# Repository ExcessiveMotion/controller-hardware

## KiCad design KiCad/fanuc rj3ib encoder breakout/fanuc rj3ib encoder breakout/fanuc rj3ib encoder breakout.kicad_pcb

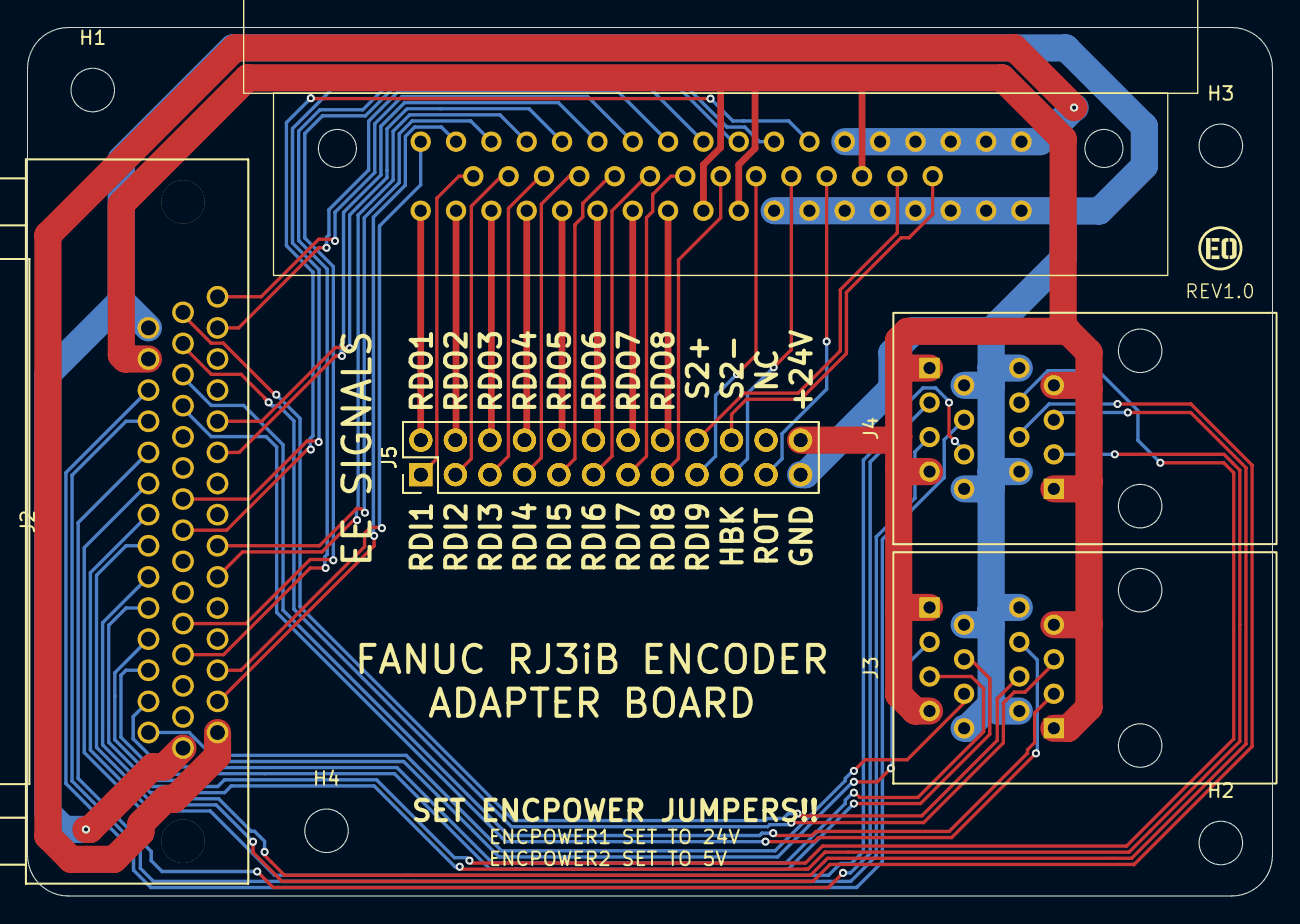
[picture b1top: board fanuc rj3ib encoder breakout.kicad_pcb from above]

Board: 2 copper layers, 91.6 x 63.9 mm, 10 parts (0 on the bottom side), 52 nets.

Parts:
H1, H2, H3, H4: MountingHole; MountingHole_3.2mm_M3_ISO7380
J1: Conn_01x50_Pin; HONDA_MR50_MALE_RIGHT_ANGLE
J2: L77HDB44SD1CH4F; CONN_L77HDB44SD1CH4F_AMP
J3, J4: E5908-0T0343-L; RJ45_E5908-0T0343-L
J5, J5#2: Conn_02x12_Odd_Even; PinHeader_2x12_P2.54mm_Vertical

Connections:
ENC1TX/RX+: J1.1, J2.3
ENC1TX/RX-: J1.2, J2.2
ENC2TX/RX+: J1.3, J2.7
ENC2TX/RX-: J1.4, J2.6
ENC3TX/RX+: J1.5, J2.11
ENC3TX/RX-: J1.6, J2.10
ENC4TX/RX+: J1.7, J2.15
ENC4TX/RX-: J1.8, J2.14
ENC5TX/RX+: J1.9, J2.20
ENC5TX/RX-: J1.10, J2.19
ENC6TX/RX+: J1.11, J2.24
ENC6TX/RX-: J1.12, J2.23
ENC7RX+: J2.30, J3.4
ENC7RX-: J2.29, J3.5
ENC7TX/RX+: J2.28, J3.3
ENC7TX/RX-: J2.27, J3.6
ENC8RX+: J2.34, J3.12
ENC8RX-: J2.33, J3.13
ENC8TX/RX+: J2.32, J3.11
ENC8TX/RX-: J2.31, J3.14
ENC9RX+: J2.38, J4.4
ENC9RX-: J2.37, J4.5
ENC9TX/RX+: J2.36, J4.3
ENC9TX/RX-: J2.35, J4.6
ENC10RX+: J2.42, J4.12
ENC10RX-: J2.41, J4.13
ENC10TX/RX+: J2.40, J4.11
ENC10TX/RX-: J2.39, J4.14
ENCPOWER1: J1.30, J1.41, J1.42, J2.43, J3.1, J3.7, J3.9, J3.15, J4.1, J4.7, J4.9, J4.15, J5.24, J5#2.24
ENCPOWER2: J1.13, J1.14, J1.15, J1.16, J1.17, J1.18, J2.1
GND: J1.43, J1.44, J1.45, J1.46, J1.47, J1.48, J1.49, J1.50, J2.16, J2.44, J3.2, J3.8, J3.10, J3.16, J4.2, J4.8, J4.10, J4.16, J5.23, J5#2.23
HBK: J1.28, J5.19, J5#2.19
RDI1: J1.19, J5.1, J5#2.1
RDI2: J1.20, J5.3, J5#2.3
RDI3: J1.21, J5.5, J5#2.5
RDI4: J1.22, J5.7, J5#2.7
RDI5: J1.23, J5.9, J5#2.9
RDI6: J1.24, J5.11, J5#2.11
RDI7: J1.25, J5.13, J5#2.13
RDI8: J1.26, J5.15, J5#2.15
RDI9(PPABN): J1.27, J5.17, J5#2.17
RDO1: J1.33, J5.2, J5#2.2
RDO2: J1.34, J5.4, J5#2.4
RDO3: J1.35, J5.6, J5#2.6
RDO4: J1.36, J5.8, J5#2.8
RDO5: J1.37, J5.10, J5#2.10
RDO6: J1.38, J5.12, J5#2.12
RDO7: J1.39, J5.14, J5#2.14
RDO8: J1.40, J5.16, J5#2.16
ROT: J1.29, J5.21, J5#2.21
S2+: J1.31, J5.18, J5#2.18
S2-: J1.32, J5.20, J5#2.20

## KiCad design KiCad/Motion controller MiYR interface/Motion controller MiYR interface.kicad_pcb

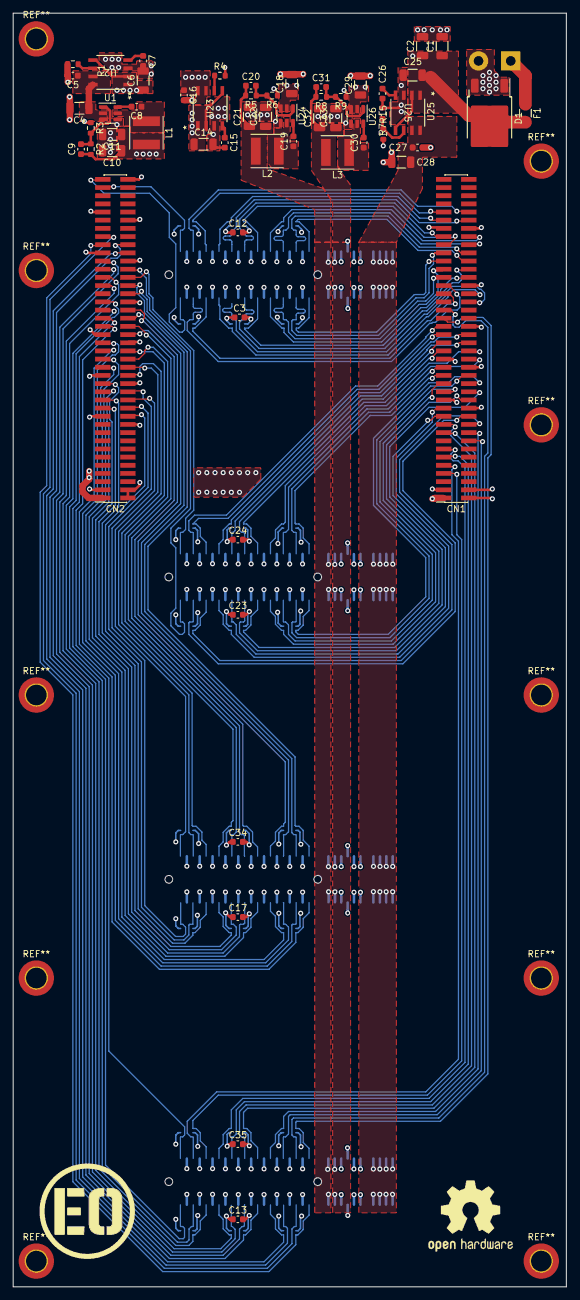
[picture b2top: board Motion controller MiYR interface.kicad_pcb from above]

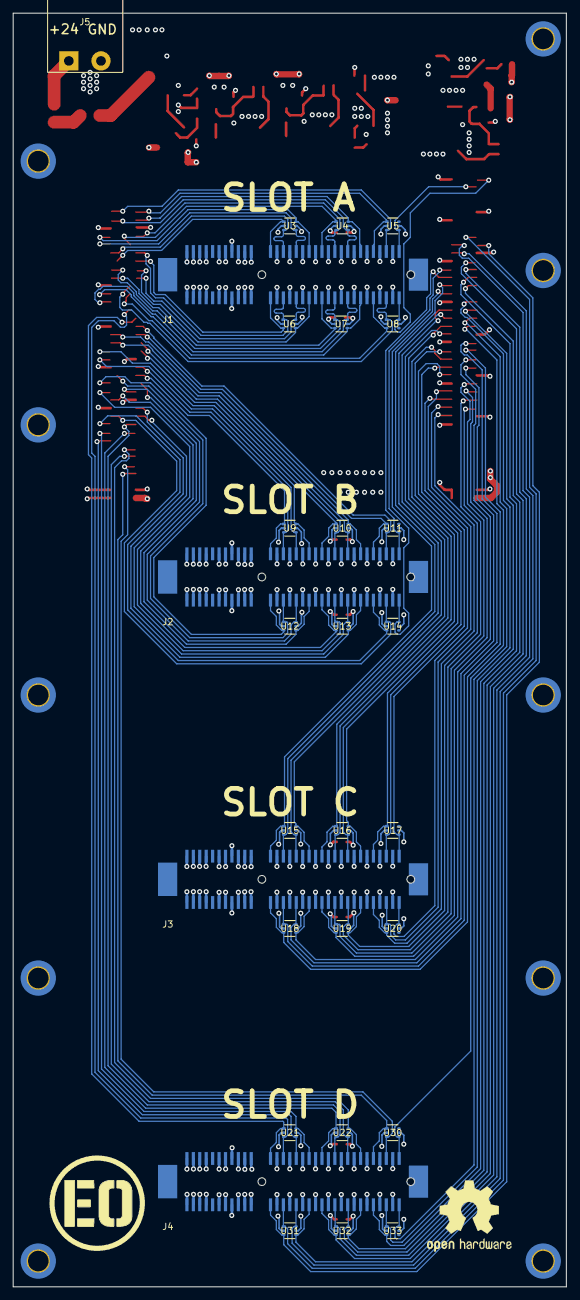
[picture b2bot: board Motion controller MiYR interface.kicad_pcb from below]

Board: 4 copper layers, 86.0 x 198.0 mm, 87 parts (29 on the bottom side), 113 nets.

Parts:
C1, C2, C4, C6, C10, C11, C14, C18, C21, C22, C25, C28, C29, C32, C33: 10uf; C_1206_3216Metric
C3, C5, C7, C8, C12, C13, C15, C16, C17, C19, C23, C24, C26, C27, C30, C34, C35: .1uf; C_0603_1608Metric
C9, C20, C31: 100pf; C_0603_1608Metric
CN1, CN2: Conn_02x40_Odd_Even; PinHeader_2x40_P1.27mm_Vertical_SMD_FLIPPED
D1: D; TO-252-3_TabPin2
F1: 10A; Fuse_1206_3216Metric
J1, J2, J3, J4: 10061913-111PLF; PCI_64_SMD_CONNECTOR
J5: Conn_01x02_Pin; 1x02_P5.00mm_Horizontal_terminal_block
L1, L2: 10uH; L_Taiyo-Yuden_MD-5050
L3: 6.8uH; L_Taiyo-Yuden_MD-5050
R1, R4, R7, R15: 100k; R_0603_1608Metric
R2: 158k; R_0603_1608Metric
R3, R6, R9: 30.1k; R_0603_1608Metric
R5: 158K; R_0603_1608Metric
R8: 93.1k; R_0603_1608Metric
U1, U24, U26: AP63201WU; TSOT-23-6
U2, U23, U25: AOZ1360AIL; AOZ1360AIL_AOS
U3, U4, U5, U6, U7, U8, U9, U10, U11, U12, U13, U14, U15, U16, U17, U18, U19, U20, U21, U22, U30, U31, U32, U33: D1213A-04S-7; SOT-363_DIO

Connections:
+3.3V: C3.1, C12.1, C13.1, C17.1, C23.1, C24.1, C34.1, C35.1, CN1.3, CN2.3, U3.5 (VCC), U4.5 (VCC), U5.5 (VCC), U6.5 (VCC), U7.5 (VCC), U8.5 (VCC), U9.5 (VCC), U10.5 (VCC), U11.5 (VCC), U12.5 (VCC), U13.5 (VCC), U14.5 (VCC), U15.5 (VCC), U16.5 (VCC), U17.5 (VCC), U18.5 (VCC), U19.5 (VCC), U20.5 (VCC), U21.5 (VCC), U22.5 (VCC), U30.5 (VCC), U31.5 (VCC), U32.5 (VCC), U33.5 (VCC)
+3.3VP: C31.1, C32.1, C33.1, J1.P$A10 (A10), J1.P$B10 (B10), J2.P$A10 (A10), J2.P$B10 (B10), J3.P$A10 (A10), J3.P$B10 (B10), J4.P$A10 (A10), J4.P$B10 (B10), L3.2, R8.2
+5V: C9.1, C10.1, C11.1, CN1.1, CN2.1, L1.2, R2.2
+5VP: C20.1, C21.1, C22.1, J1.P$A11 (A11), J1.P$B11 (B11), J2.P$A11 (A11), J2.P$B11 (B11), J3.P$A11 (A11), J3.P$B11 (B11), J4.P$A11 (A11), J4.P$B11 (B11), L2.2, R5.2
+24V: C1.1, C2.1, C6.1, C14.1, C25.1, D1.1 (K), F1.2, U2.1 (IN), U2.2 (IN), U2.5 (EN), U23.1 (IN), U23.2 (IN), U23.5 (EN), U25.1 (IN), U25.2 (IN), U25.5 (EN)
GND: C1.2, C2.2, C3.2, C4.2, C5.2, C6.2, C7.2, C10.2, C11.2, C12.2, C13.2, C14.2, C15.2, C16.2, C17.2, C18.2, C21.2, C22.2, C23.2, C24.2, C25.2, C26.2, C27.2, C28.2, C29.2, C32.2, C33.2, C34.2, C35.2, CN1.2, CN1.4, CN1.24, CN1.25, CN1.34, CN1.35, CN1.44, CN1.54, CN1.67, CN1.68, CN2.2, CN2.4, CN2.20, CN2.21, CN2.30, CN2.31, CN2.40, CN2.41, CN2.50, CN2.60, CN2.61, CN2.70, CN2.71, CN2.80, D1.2 (A), J1.P$A6 (A6), J1.P$A7 (A7), J1.P$A8 (A8), J1.P$A9 (A9), J1.P$A13 (A13), J1.P$A15 (A15), J1.P$A17 (A17), J1.P$A19 (A19), J1.P$A21 (A21), J1.P$A23 (A23), J1.P$A25 (A25), J1.P$A27 (A27), J1.P$A29 (A29), J1.P$A31 (A31), J1.P$B6 (B6), J1.P$B7 (B7), J1.P$B8 (B8), J1.P$B9 (B9), J1.P$B13 (B13), J1.P$B15 (B15), J1.P$B17 (B17), J1.P$B19 (B19), J1.P$B21 (B21), J1.P$B23 (B23), J1.P$B25 (B25), J1.P$B27 (B27), J1.P$B29 (B29), J1.P$B31 (B31), J2.P$A6 (A6), J2.P$A7 (A7), J2.P$A8 (A8), J2.P$A9 (A9), J2.P$A13 (A13), J2.P$A15 (A15), J2.P$A17 (A17), J2.P$A19 (A19), J2.P$A21 (A21), J2.P$A23 (A23), J2.P$A25 (A25), J2.P$A27 (A27), J2.P$A29 (A29), J2.P$A31 (A31), J2.P$B6 (B6), J2.P$B7 (B7), J2.P$B8 (B8), J2.P$B9 (B9), J2.P$B13 (B13), J2.P$B15 (B15), J2.P$B17 (B17), J2.P$B19 (B19), J2.P$B21 (B21), J2.P$B23 (B23), J2.P$B25 (B25), J2.P$B27 (B27), J2.P$B29 (B29), J2.P$B31 (B31), J3.P$A6 (A6), J3.P$A7 (A7), J3.P$A8 (A8), J3.P$A9 (A9), J3.P$A13 (A13), J3.P$A15 (A15), J3.P$A17 (A17), J3.P$A19 (A19), J3.P$A21 (A21), J3.P$A23 (A23), J3.P$A25 (A25), J3.P$A27 (A27), J3.P$A29 (A29), J3.P$A31 (A31), J3.P$B6 (B6), J3.P$B7 (B7), J3.P$B8 (B8), J3.P$B9 (B9), J3.P$B13 (B13), J3.P$B15 (B15), J3.P$B17 (B17), J3.P$B19 (B19), J3.P$B21 (B21), J3.P$B23 (B23), J3.P$B25 (B25), J3.P$B27 (B27), J3.P$B29 (B29), J3.P$B31 (B31), J4.P$A6 (A6), J4.P$A7 (A7), J4.P$A8 (A8), J4.P$A9 (A9), J4.P$A13 (A13), J4.P$A15 (A15), J4.P$A17 (A17), J4.P$A19 (A19), J4.P$A21 (A21), J4.P$A23 (A23), J4.P$A25 (A25), J4.P$A27 (A27), J4.P$A29 (A29), J4.P$A31 (A31), J4.P$B6 (B6), J4.P$B7 (B7), J4.P$B8 (B8), J4.P$B9 (B9), J4.P$B13 (B13), J4.P$B15 (B15), J4.P$B17 (B17), J4.P$B19 (B19), J4.P$B21 (B21), J4.P$B23 (B23), J4.P$B25 (B25), J4.P$B27 (B27), J4.P$B29 (B29), J4.P$B31 (B31), J5.2, R1.2, R3.1, R4.2, R6.1, R7.2, R9.1, R15.2, U1.4 (GND), U2.3 (GND), U3.2 (GND), U4.2 (GND), U5.2 (GND), U6.2 (GND), U7.2 (GND), U8.2 (GND), U9.2 (GND), U10.2 (GND), U11.2 (GND), U12.2 (GND), U13.2 (GND), U14.2 (GND), U15.2 (GND), U16.2 (GND), U17.2 (GND), U18.2 (GND), U19.2 (GND), U20.2 (GND), U21.2 (GND), U22.2 (GND), U23.3 (GND), U24.4 (GND), U25.3 (GND), U26.4 (GND), U30.2 (GND), U31.2 (GND), U32.2 (GND), U33.2 (GND)
unnamed: F1.1, J5.1
unnamed: C8.2, U1.6 (BST)
unnamed: C4.1, C5.1, U1.2 (EN), U1.3 (IN), U2.7 (OUT), U2.8 (OUT)
unnamed: C9.2, R2.1, R3.2, U1.1 (FB)
unnamed: C8.1, L1.1, U1.5 (SW)
unnamed: R1.1, U2.6 (SET)
unnamed: C7.1, U2.4 (SS)
unnamed: R4.1, U23.6 (SET)
unnamed: C15.1, U23.4 (SS)
unnamed: C19.2, U24.6 (BST)
unnamed: C16.1, C18.1, C29.1, U23.7 (OUT), U23.8 (OUT), U24.2 (EN), U24.3 (IN), U26.2 (EN), U26.3 (IN)
unnamed: C20.2, R5.1, R6.2, U24.1 (FB)
unnamed: C19.1, L2.1, U24.5 (SW)
unnamed: R7.1, R15.1, U25.6 (SET)
unnamed: C26.1, U25.4 (SS)
unnamed: C30.2, U26.6 (BST)
unnamed: C31.2, R8.1, R9.2, U26.1 (FB)
unnamed: C30.1, L3.1, U26.5 (SW)
SLOT A 24V: C27.1, C28.1, J1.P$A1 (A1), J1.P$A2 (A2), J1.P$A3 (A3), J1.P$A4 (A4), J1.P$B1 (B1), J1.P$B2 (B2), J1.P$B3 (B3), J1.P$B4 (B4), J2.P$A1 (A1), J2.P$A2 (A2), J2.P$A3 (A3), J2.P$A4 (A4), J2.P$B1 (B1), J2.P$B2 (B2), J2.P$B3 (B3), J2.P$B4 (B4), J3.P$A1 (A1), J3.P$A2 (A2), J3.P$A3 (A3), J3.P$A4 (A4), J3.P$B1 (B1), J3.P$B2 (B2), J3.P$B3 (B3), J3.P$B4 (B4), J4.P$A1 (A1), J4.P$A2 (A2), J4.P$A3 (A3), J4.P$A4 (A4), J4.P$B1 (B1), J4.P$B2 (B2), J4.P$B3 (B3), J4.P$B4 (B4), U25.7 (OUT), U25.8 (OUT)
SLOTA1N: CN1.62, J1.P$A14 (A14), U3.3 (CH2)
SLOTA1P: CN1.60, J1.P$A12 (A12), U3.1 (CH1)
SLOTA2N: CN1.66, J1.P$A18 (A18), U3.6 (CH4)
SLOTA2P: CN1.64, J1.P$A16 (A16), U3.4 (CH3)
SLOTA3N: CN1.65, J1.P$A22 (A22), U4.3 (CH2)
SLOTA3P: CN1.63, J1.P$A20 (A20), U4.1 (CH1)
SLOTA4N: CN1.69, J1.P$A26 (A26), U4.6 (CH4)
SLOTA4P: CN1.70, J1.P$A24 (A24), U4.4 (CH3)
SLOTA5N: CN1.72, J1.P$A30 (A30), U5.3 (CH2)
SLOTA5P: CN1.71, J1.P$A28 (A28), U5.1 (CH1)
SLOTA6N: CN1.61, J1.P$B14 (B14), U6.1 (CH1)
SLOTA6P: CN1.59, J1.P$B12 (B12), U6.3 (CH2)
SLOTA7N: CN1.57, J1.P$B18 (B18), U6.4 (CH3)
SLOTA7P: CN1.55, J1.P$B16 (B16), U6.6 (CH4)
SLOTA8N: CN1.58, J1.P$B22 (B22), U7.1 (CH1)
SLOTA8P: CN1.56, J1.P$B20 (B20), U7.3 (CH2)
SLOTA9N: CN1.52, J1.P$B26 (B26), U7.4 (CH3)
SLOTA9P: CN1.50, J1.P$B24 (B24), U7.6 (CH4)
SLOTA10N: CN1.53, J1.P$B30 (B30), U8.1 (CH1)
SLOTA10P: CN1.51, J1.P$B28 (B28), U8.3 (CH2)
SLOTA11N: CN2.79, J1.P$B32 (B32), U8.6 (CH4)
SLOTA11P: CN2.77, J1.P$A32 (A32), U5.4 (CH3)
SLOTB1N: CN1.33, J2.P$A14 (A14), U9.3 (CH2)
SLOTB1P: CN1.31, J2.P$A12 (A12), U9.1 (CH1)
SLOTB2N: CN1.38, J2.P$A18 (A18), U9.6 (CH4)
SLOTB2P: CN1.36, J2.P$A16 (A16), U9.4 (CH3)
SLOTB3N: CN1.39, J2.P$A22 (A22), U10.3 (CH2)
SLOTB3P: CN1.37, J2.P$A20 (A20), U10.1 (CH1)
SLOTB4N: CN1.42, J2.P$A26 (A26), U10.6 (CH4)
SLOTB4P: CN1.40, J2.P$A24 (A24), U10.4 (CH3)
SLOTB5N: CN1.43, J2.P$A30 (A30), U11.3 (CH2)
SLOTB5P: CN1.41, J2.P$A28 (A28), U11.1 (CH1)
SLOTB6N: CN1.32, J2.P$B14 (B14), U12.1 (CH1)
SLOTB6P: CN1.30, J2.P$B12 (B12), U12.3 (CH2)
SLOTB7N: CN1.29, J2.P$B18 (B18), U12.4 (CH3)
SLOTB7P: CN1.27, J2.P$B16 (B16), U12.6 (CH4)
SLOTB8N: CN1.28, J2.P$B22 (B22), U13.1 (CH1)
SLOTB8P: CN1.26, J2.P$B20 (B20), U13.3 (CH2)
SLOTB9N: CN1.23, J2.P$B26 (B26), U13.4 (CH3)
SLOTB9P: CN1.21, J2.P$B24 (B24), U13.6 (CH4)
SLOTB10N: CN1.22, J2.P$B30 (B30), U14.1 (CH1)
SLOTB10P: CN1.20, J2.P$B28 (B28), U14.3 (CH2)
SLOTB11N: CN2.58, J2.P$B32 (B32), U14.6 (CH4)
SLOTB11P: CN2.56, J2.P$A32 (A32), U11.4 (CH3)
SLOTC1N: CN2.54, J3.P$A14 (A14), U15.3 (CH2)
SLOTC1P: CN2.52, J3.P$A12 (A12), U15.1 (CH1)
SLOTC2N: CN2.48, J3.P$A18 (A18), U15.6 (CH4)
SLOTC2P: CN2.46, J3.P$A16 (A16), U15.4 (CH3)
SLOTC3N: CN2.44, J3.P$A22 (A22), U16.3 (CH2)
SLOTC3P: CN2.42, J3.P$A20 (A20), U16.1 (CH1)
SLOTC4N: CN2.38, J3.P$A26 (A26), U16.6 (CH4)
SLOTC4P: CN2.36, J3.P$A24 (A24), U16.4 (CH3)
SLOTC5N: CN2.34, J3.P$A30 (A30), U17.3 (CH2)
SLOTC5P: CN2.32, J3.P$A28 (A28), U17.1 (CH1)
SLOTC6N: CN2.39, J3.P$B14 (B14), U18.1 (CH1)
SLOTC6P: CN2.37, J3.P$B12 (B12), U18.3 (CH2)
SLOTC7N: CN2.35, J3.P$B18 (B18), U18.4 (CH3)
SLOTC7P: CN2.33, J3.P$B16 (B16), U18.6 (CH4)
SLOTC8N: CN2.29, J3.P$B22 (B22), U19.1 (CH1)
SLOTC8P: CN2.27, J3.P$B20 (B20), U19.3 (CH2)
SLOTC9N: CN2.25, J3.P$B26 (B26), U19.4 (CH3)
SLOTC9P: CN2.23, J3.P$B24 (B24), U19.6 (CH4)
SLOTC10N: CN2.24, J3.P$B30 (B30), U20.1 (CH1)
SLOTC10P: CN2.22, J3.P$B28 (B28), U20.3 (CH2)
SLOTC11N: CN2.28, J3.P$B32 (B32), U20.6 (CH4)
SLOTC11P: CN2.26, J3.P$A32 (A32), U17.4 (CH3)
SLOTD1N: CN1.47, J4.P$A14 (A14), U21.3 (CH2)
SLOTD1P: CN1.45, J4.P$A12 (A12), U21.1 (CH1)
SLOTD2N: CN1.18, J4.P$A18 (A18), U21.6 (CH4)
SLOTD2P: CN1.16, J4.P$A16 (A16), U21.4 (CH3)
SLOTD3N: CN1.19, J4.P$A22 (A22), U22.3 (CH2)
SLOTD3P: CN1.17, J4.P$A20 (A20), U22.1 (CH1)
SLOTD4N: CN1.13, J4.P$A26 (A26), U22.6 (CH4)
SLOTD4P: CN1.11, J4.P$A24 (A24), U22.4 (CH3)
SLOTD5N: CN1.9, J4.P$A30 (A30), U30.3 (CH2)
SLOTD5P: CN1.7, J4.P$A28 (A28), U30.1 (CH1)
SLOTD6N: CN2.65, J4.P$B14 (B14), U31.1 (CH1)
SLOTD6P: CN2.63, J4.P$B12 (B12), U31.3 (CH2)
SLOTD7N: CN2.64, J4.P$B18 (B18), U31.4 (CH3)
SLOTD7P: CN2.62, J4.P$B16 (B16), U31.6 (CH4)
SLOTD8N: CN2.59, J4.P$B22 (B22), U32.1 (CH1)
SLOTD8P: CN2.57, J4.P$B20 (B20), U32.3 (CH2)
SLOTD9N: CN2.55, J4.P$B26 (B26), U32.4 (CH3)
SLOTD9P: CN2.53, J4.P$B24 (B24), U32.6 (CH4)
SLOTD10N: CN2.49, J4.P$B30 (B30), U33.1 (CH1)
SLOTD10P: CN2.47, J4.P$B28 (B28), U33.3 (CH2)
SLOTD11N: CN2.45, J4.P$B32 (B32), U33.6 (CH4)
SLOTD11P: CN2.43, J4.P$A32 (A32), U30.4 (CH3)

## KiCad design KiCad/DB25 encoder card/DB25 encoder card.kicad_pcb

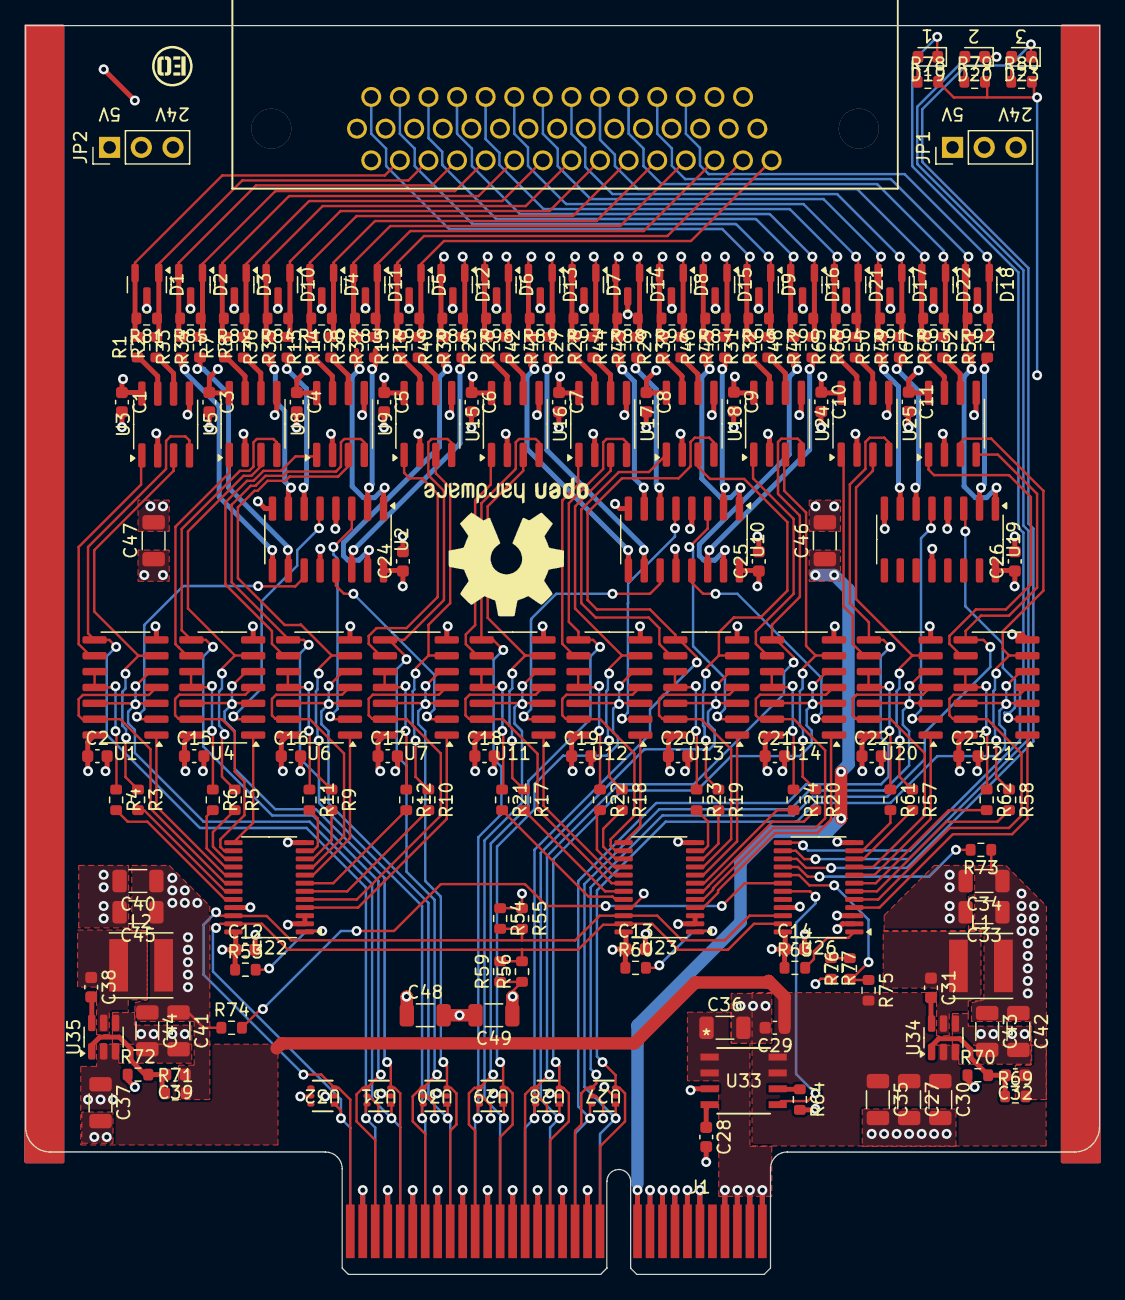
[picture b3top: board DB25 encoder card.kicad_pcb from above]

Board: 4 copper layers, 86.0 x 100.0 mm, 213 parts (0 on the bottom side), 213 nets.

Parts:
C1, C2, C3, C4, C5, C6, C7, C8, C9, C10, C11, C12, C13, C14, C15, C16, C17, C18, C19, C20, C21, C22, C23, C24, C25, C26, C28, C29, C31, C38: .1uf; C_0603_1608Metric
C27, C30, C33, C34, C35, C36, C37, C40, C41, C42, C43, C44, C45, C46, C47, C48, C49: 10uf; C_1206_3216Metric
C32, C39: 100pf; C_0603_1608Metric
D1, D2, D3, D4, D5, D6, D7, D8, D9, D10, D11, D12, D13, D14, D15, D16, D17, D18, D21, D22: SM712_SOT23; SOT-23
D19, D20, D23: LED; LED_0603_1608Metric
J1: Motion Controller Interface; 64pin card
J2: L77HDB44SD1CH4F; CONN_L77HDB44SD1CH4F_AMP
JP1, JP2: Jumper_3_Bridged12; PinHeader_1x03_P2.54mm_Vertical
L1, L2: 10uH; L_Taiyo-Yuden_MD-5050
R1, R2, R7, R8, R13, R14, R15, R16, R25, R26, R27, R28, R29, R30, R31, R32, R33, R34, R35, R36, R37, R38, R39, R40, R41, R42, R43, R44, R45, R46, R47, R48, R49, R50, R51, R52, R65, R66, R67, R68: 10; R_0603_1608Metric
R3, R4, R5, R6, R9, R10, R11, R12, R17, R18, R19, R20, R21, R22, R23, R24, R53, R54, R55, R56, R57, R58, R59, R60, R61, R62, R63, R73, R74, R76, R77: 10K; R_0603_1608Metric
R64: 100k; R_0603_1608Metric
R69, R71, R75: 158K; R_0603_1608Metric
R70, R72: 30.1k; R_0603_1608Metric
R78, R79, R80: 10k; R_0603_1608Metric
R81, R82, R83, R84, R85, R86, R87, R88, R89, R90, R91, R92, R93, R94, R95, R96, R97, R98, R99, R100: 120; R_0603_1608Metric
U1, U4, U6, U7, U11, U12, U13, U14, U20, U21: 74LVC125; SOIC-14_3.9x8.7mm_P1.27mm
U2, U10, U19: AM26LV32xD; SOIC-16_3.9x9.9mm_P1.27mm
U3, U5, U8, U9, U15, U16, U17, U18, U24, U25: THVD1420D; SOIC-8_3.9x4.9mm_P1.27mm
U22, U23, U26: TCA9555PWR; TSSOP-24_4.4x7.8mm_P0.65mm
U27, U28, U29, U30, U31, U32: D1213A-04S-7; SOT-363_DIO
U33: AOZ1360AIL; AOZ1360AIL_AOS
U34, U35: AP63201WU; TSOT-23-6

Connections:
1N: J1.1N, U21.8, U25.4 (DI), U27.4 (CH3)
1P: J1.1P, U21.3, U21.5, U21.12, U27.3 (CH2)
2N: J1.2N, U14.8, U18.4 (DI), U28.4 (CH3)
2P: J1.2P, U14.3, U14.5, U14.12, U28.3 (CH2)
3N: J1.3N, U12.8, U16.4 (DI), U29.4 (CH3)
3P: J1.3P, U12.3, U12.5, U12.12, U29.3 (CH2)
4N: J1.4N, U7.8, U9.4 (DI), U30.4 (CH3)
4P: J1.4P, U7.3, U7.5, U7.12, U30.3 (CH2)
5.5V1: C32.1, C33.1, C34.1, C42.1, C43.1, JP1.1 (A), L1.2, R69.2, R73.1
5.5V1_OK: R73.2, U26.16 (P13)
5.5V2: C39.1, C40.1, C41.1, C44.1, C45.1, JP2.1 (A), L2.2, R71.2, R74.1
5.5V2_OK: R74.2, U26.18 (P15)
5N: J1.5N, U4.8, U5.4 (DI), U31.4 (CH3)
5P: J1.5P, U4.3, U4.5, U4.12, U31.3 (CH2)
6N: J1.6N, U20.8, U24.4 (DI), U27.6 (CH4)
6P: J1.6P, U20.3, U20.5, U20.12, U27.1 (CH1)
7N: J1.7N, U13.8, U17.4 (DI), U28.6 (CH4)
7P: J1.7P, U13.3, U13.5, U13.12, U28.1 (CH1)
8N: J1.8N, U11.8, U15.4 (DI), U29.6 (CH4)
8P: J1.8P, U11.3, U11.5, U11.12, U29.1 (CH1)
9N: J1.9N, U6.8, U8.4 (DI), U30.6 (CH4)
9P: J1.9P, U6.3, U6.5, U6.12, U30.1 (CH1)
10N: J1.10N, U1.8, U3.4 (DI), U31.6 (CH4)
10P: J1.10P, U1.3, U1.5, U1.12, U31.1 (CH1)
11N: J1.11N, R56.2, R59.2, U22.23 (SDA), U23.23 (SDA), U26.23 (SDA), U32.1 (CH1)
11P: J1.11P, R54.2, R55.2, U22.22 (SCL), U23.22 (SCL), U26.22 (SCL), U32.3 (CH2)
24VFUSED: C27.1, C29.1, C30.1, C35.1, C37.1, JP1.3 (B), JP2.3 (B), R75.2, U33.7 (OUT), U33.8 (OUT), U34.2 (EN), U34.3 (IN), U35.2 (EN), U35.3 (IN)
24VFUSED_OK: R75.1, R76.1, U26.17 (P14)
24V_EN: U26.19 (P16), U33.5 (EN)
+3.3V: C2.1, C12.1, C13.1, C14.1, C15.1, C16.1, C17.1, C18.1, C19.1, C20.1, C21.1, C22.1, C23.1, C48.1, C49.1, J1.3.3V, R53.1, R54.1, R55.1, R56.1, R59.1, R60.1, R63.1, U1.14 (VCC), U4.14 (VCC), U6.14 (VCC), U7.14 (VCC), U11.14 (VCC), U12.14 (VCC), U13.14 (VCC), U14.14 (VCC), U20.14 (VCC), U21.14 (VCC), U22.24 (VCC), U23.21 (A0), U23.24 (VCC), U26.2 (A1), U26.24 (VCC), U27.5 (VCC), U28.5 (VCC), U29.5 (VCC), U30.5 (VCC), U31.5 (VCC), U32.5 (VCC)
+5V: C1.1, C3.1, C4.1, C5.1, C6.1, C7.1, C8.1, C9.1, C10.1, C11.1, C24.1, C25.1, C26.1, C46.1, C47.1, J1.5V, R78.2, R79.2, R80.2, U2.4 (G), U2.16 (VDD), U3.8 (VCC), U5.8 (VCC), U8.8 (VCC), U9.8 (VCC), U10.4 (G), U10.16 (VDD), U15.8 (VCC), U16.8 (VCC), U17.8 (VCC), U18.8 (VCC), U19.4 (G), U19.16 (VDD), U24.8 (VCC), U25.8 (VCC)
+24V: C36.1, J1.24V, U33.1 (IN), U33.2 (IN)
CONFIG1_1: U1.4, U1.13, U22.18 (P15)
CONFIG1_2: R3.2, U22.19 (P16)
CONFIG1_3: U1.1, U22.17 (P14)
CONFIG1_4: R4.2, U22.20 (P17)
CONFIG2_1: U4.4, U4.13, U22.14 (P11)
CONFIG2_2: R5.2, U22.15 (P12)
CONFIG2_3: U4.1, U22.13 (P10)
CONFIG2_4: R6.2, U22.16 (P13)
CONFIG3_1: U6.4, U6.13, U22.9 (P05)
CONFIG3_2: R9.2, U22.10 (P06)
CONFIG3_3: U6.1, U22.8 (P04)
CONFIG3_4: R11.2, U22.11 (P07)
CONFIG4_1: U7.4, U7.13, U22.5 (P01)
CONFIG4_2: R10.2, U22.6 (P02)
CONFIG4_3: U7.1, U22.4 (P00)
CONFIG4_4: R12.2, U22.7 (P03)
CONFIG5_1: U11.4, U11.13, U23.18 (P15)
CONFIG5_2: R17.2, U23.19 (P16)
CONFIG5_3: U11.1, U23.17 (P14)
CONFIG5_4: R21.2, U23.20 (P17)
CONFIG6_1: U12.4, U12.13, U23.14 (P11)
CONFIG6_2: R18.2, U23.15 (P12)
CONFIG6_3: U12.1, U23.13 (P10)
CONFIG6_4: R22.2, U23.16 (P13)
CONFIG7_1: U13.4, U13.13, U23.9 (P05)
CONFIG7_2: R19.2, U23.10 (P06)
CONFIG7_3: U13.1, U23.8 (P04)
CONFIG7_4: R23.2, U23.11 (P07)
CONFIG8_1: U14.4, U14.13, U23.5 (P01)
CONFIG8_2: R20.2, U23.6 (P02)
CONFIG8_3: U14.1, U23.4 (P00)
CONFIG8_4: R24.2, U23.7 (P03)
CONFIG9_1: U20.4, U20.13, U26.9 (P05)
CONFIG9_2: R57.2, U26.10 (P06)
CONFIG9_3: U20.1, U26.8 (P04)
CONFIG9_4: R61.2, U26.11 (P07)
CONFIG10_1: U21.4, U21.13, U26.5 (P01)
CONFIG10_2: R58.2, U26.6 (P02)
CONFIG10_3: U21.1, U26.4 (P00)
CONFIG10_4: R62.2, U26.7 (P03)
ENC1RX+: D2.1 (A1), J2.5, R34.2, R85.1
ENC1RX-: D2.2 (A2), J2.4, R33.2, R85.2
ENC1TX/RX+: D1.1 (A1), J2.3, R2.2, R81.1
ENC1TX/RX-: D1.2 (A2), J2.2, R1.2, R81.2
ENC2RX+: D10.1 (A1), J2.9, R35.2, R84.1
ENC2RX-: D10.2 (A2), J2.8, R36.2, R84.2
ENC2TX/RX+: D3.1 (A1), J2.7, R8.2, R82.1
ENC2TX/RX-: D3.2 (A2), J2.6, R7.2, R82.2
ENC3RX+: D11.1 (A1), J2.13, R37.2, R83.1
ENC3RX-: D11.2 (A2), J2.12, R38.2, R83.2
ENC3TX/RX+: D4.1 (A1), J2.11, R14.2, R100.1
ENC3TX/RX-: D4.2 (A2), J2.10, R13.2, R100.2
ENC4RX+: D12.1 (A1), J2.18, R39.2, R86.1
ENC4RX-: D12.2 (A2), J2.17, R40.2, R86.2
ENC4TX/RX+: D5.1 (A1), J2.15, R16.2, R99.1
ENC4TX/RX-: D5.2 (A2), J2.14, R15.2, R99.2
ENC5RX+: D13.1 (A1), J2.22, R41.2, R89.1
ENC5RX-: D13.2 (A2), J2.21, R42.2, R89.2
ENC5TX/RX+: D6.1 (A1), J2.20, R26.2, R98.1
ENC5TX/RX-: D6.2 (A2), J2.19, R25.2, R98.2
ENC6RX+: D14.1 (A1), J2.26, R43.2, R88.1
ENC6RX-: D14.2 (A2), J2.25, R44.2, R88.2
ENC6TX/RX+: D7.1 (A1), J2.24, R28.2, R97.1
ENC6TX/RX-: D7.2 (A2), J2.23, R27.2, R97.2
ENC7RX+: D15.1 (A1), J2.30, R45.2, R87.1
ENC7RX-: D15.2 (A2), J2.29, R46.2, R87.2
ENC7TX/RX+: D8.1 (A1), J2.28, R30.2, R96.1
ENC7TX/RX-: D8.2 (A2), J2.27, R29.2, R96.2
ENC8RX+: D16.1 (A1), J2.34, R47.2, R90.1
ENC8RX-: D16.2 (A2), J2.33, R48.2, R90.2
ENC8TX/RX+: D9.1 (A1), J2.32, R32.2, R95.1
ENC8TX/RX-: D9.2 (A2), J2.31, R31.2, R95.2
ENC9RX+: D17.1 (A1), J2.38, R49.2, R91.1
ENC9RX-: D17.2 (A2), J2.37, R50.2, R91.2
ENC9TX/RX+: D21.1 (A1), J2.36, R66.2, R94.1
ENC9TX/RX-: D21.2 (A2), J2.35, R65.2, R94.2
ENC10RX+: D18.1 (A1), J2.42, R51.2, R92.1
ENC10RX-: D18.2 (A2), J2.41, R52.2, R92.2
ENC10TX/RX+: D22.1 (A1), J2.40, R68.2, R93.1
ENC10TX/RX-: D22.2 (A2), J2.39, R67.2, R93.2
ENCPOWER1: J2.43, JP1.2 (C)
ENCPOWER2: J2.1, JP2.2 (C)
GND: C1.2, C2.2, C3.2, C4.2, C5.2, C6.2, C7.2, C8.2, C9.2, C10.2, C11.2, C12.2, C13.2, C14.2, C15.2, C16.2, C17.2, C18.2, C19.2, C20.2, C21.2, C22.2, C23.2, C24.2, C25.2, C26.2, C27.2, C28.2, C29.2, C30.2, C33.2, C34.2, C35.2, C36.2, C37.2, C40.2, C41.2, C42.2, C43.2, C44.2, C45.2, C46.2, C47.2, C48.2, C49.2, D1.3 (common), D2.3 (common), D3.3 (common), D4.3 (common), D5.3 (common), D6.3 (common), D7.3 (common), D8.3 (common), D9.3 (common), D10.3 (common), D11.3 (common), D12.3 (common), D13.3 (common), D14.3 (common), D15.3 (common), D16.3 (common), D17.3 (common), D18.3 (common), D21.3 (common), D22.3 (common), J1.GND, J2.16, J2.44, R64.2, R70.1, R72.1, R77.2, U1.7 (GND), U2.8 (GND), U2.12 (~G), U3.2 (~RE), U3.5 (GND), U4.7 (GND), U5.2 (~RE), U5.5 (GND), U6.7 (GND), U7.7 (GND), U8.2 (~RE), U8.5 (GND), U9.2 (~RE), U9.5 (GND), U10.8 (GND), U10.12 (~G), U11.7 (GND), U12.7 (GND), U13.7 (GND), U14.7 (GND), U15.2 (~RE), U15.5 (GND), U16.2 (~RE), U16.5 (GND), U17.2 (~RE), U17.5 (GND), U18.2 (~RE), U18.5 (GND), U19.8 (GND), U19.12 (~G), U20.7 (GND), U21.7 (GND), U22.2 (A1), U22.3 (A2), U22.12 (GND), U22.21 (A0), U23.2 (A1), U23.3 (A2), U23.12 (GND), U24.2 (~RE), U24.5 (GND), U25.2 (~RE), U25.5 (GND), U26.3 (A2), U26.12 (GND), U26.21 (A0), U27.2 (GND), U28.2 (GND), U29.2 (GND), U30.2 (GND), U31.2 (GND), U32.2 (GND), U33.3 (GND), U34.4 (GND), U35.4 (GND)
LED1: D19.1 (K), U26.13 (P10)
LED2: D20.1 (K), U26.14 (P11)
LED3: D23.1 (K), U26.15 (P12)
unnamed: D19.2 (A), R78.1
unnamed: D20.2 (A), R79.1
unnamed: D23.2 (A), R80.1
unnamed: R4.1, U1.10, U1.11
unnamed: R6.1, U4.10, U4.11
unnamed: R11.1, U6.10, U6.11
unnamed: R12.1, U7.10, U7.11
unnamed: R21.1, U11.10, U11.11
unnamed: R22.1, U12.10, U12.11
unnamed: R23.1, U13.10, U13.11
unnamed: R24.1, U14.10, U14.11
unnamed: R61.1, U20.10, U20.11
unnamed: R62.1, U21.10, U21.11
unnamed: R76.2, R77.1
unnamed: R37.1, U2.2 (1A)
unnamed: R38.1, U2.1 (1B)
unnamed: U2.3 (1Y), U6.2
unnamed: R35.1, U2.6 (2A)
unnamed: R36.1, U2.7 (2B)
unnamed: U2.5 (2Y), U4.2
unnamed: R34.1, U2.10 (3A)
unnamed: R33.1, U2.9 (3B)
unnamed: U1.2, U2.11 (3Y)
unnamed: R39.1, U2.14 (4A)
unnamed: R40.1, U2.15 (4B)
unnamed: U2.13 (4Y), U7.2
unnamed: R2.1, U3.6 (A)
unnamed: R1.1, U3.7 (B)
unnamed: R3.1, U1.6, U3.3 (DE)
unnamed: U1.9, U3.1 (RO)
unnamed: R8.1, U5.6 (A)
unnamed: R7.1, U5.7 (B)
unnamed: R5.1, U4.6, U5.3 (DE)
unnamed: U4.9, U5.1 (RO)
unnamed: R14.1, U8.6 (A)
unnamed: R13.1, U8.7 (B)
unnamed: R9.1, U6.6, U8.3 (DE)
unnamed: U6.9, U8.1 (RO)
unnamed: R16.1, U9.6 (A)
unnamed: R15.1, U9.7 (B)
unnamed: R10.1, U7.6, U9.3 (DE)
unnamed: U7.9, U9.1 (RO)
unnamed: R45.1, U10.2 (1A)
unnamed: R46.1, U10.1 (1B)
unnamed: U10.3 (1Y), U13.2
unnamed: R43.1, U10.6 (2A)
unnamed: R44.1, U10.7 (2B)
unnamed: U10.5 (2Y), U12.2
unnamed: R41.1, U10.10 (3A)
unnamed: R42.1, U10.9 (3B)
unnamed: U10.11 (3Y), U11.2
unnamed: R47.1, U10.14 (4A)
unnamed: R48.1, U10.15 (4B)
unnamed: U10.13 (4Y), U14.2
unnamed: R26.1, U15.6 (A)
unnamed: R25.1, U15.7 (B)
unnamed: R17.1, U11.6, U15.3 (DE)
unnamed: U11.9, U15.1 (RO)
unnamed: R28.1, U16.6 (A)
unnamed: R27.1, U16.7 (B)
unnamed: R18.1, U12.6, U16.3 (DE)
unnamed: U12.9, U16.1 (RO)
unnamed: R30.1, U17.6 (A)
unnamed: R29.1, U17.7 (B)
unnamed: R19.1, U13.6, U17.3 (DE)
unnamed: U13.9, U17.1 (RO)
unnamed: R32.1, U18.6 (A)
unnamed: R31.1, U18.7 (B)
unnamed: R20.1, U14.6, U18.3 (DE)
unnamed: U14.9, U18.1 (RO)
unnamed: R51.1, U19.2 (1A)
unnamed: R52.1, U19.1 (1B)
unnamed: U19.3 (1Y), U21.2
unnamed: R49.1, U19.6 (2A)
unnamed: R50.1, U19.7 (2B)
unnamed: U19.5 (2Y), U20.2
unnamed: R53.2, U22.1 (~INT)
unnamed: R60.2, U23.1 (~INT)
unnamed: R66.1, U24.6 (A)
unnamed: R65.1, U24.7 (B)
unnamed: R57.1, U20.6, U24.3 (DE)
unnamed: U20.9, U24.1 (RO)
unnamed: R68.1, U25.6 (A)
unnamed: R67.1, U25.7 (B)
unnamed: R58.1, U21.6, U25.3 (DE)
unnamed: U21.9, U25.1 (RO)
unnamed: R63.2, U26.1 (~INT)
unnamed: R64.1, U33.6 (SET)
unnamed: C28.1, U33.4 (SS)
unnamed: C31.2, U34.6 (BST)
unnamed: C32.2, R69.1, R70.2, U34.1 (FB)
unnamed: C31.1, L1.1, U34.5 (SW)
unnamed: C38.2, U35.6 (BST)
unnamed: C39.2, R71.1, R72.2, U35.1 (FB)
unnamed: C38.1, L2.1, U35.5 (SW)

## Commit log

2023-09-10 create base project and file system
2023-10-06 create schematic and PCB
2023-10-06 update gitignore
2023-10-09 10ch encoder card
2025-09-05 update controller boards
